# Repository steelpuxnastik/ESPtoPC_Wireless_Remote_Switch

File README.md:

# ESPtoPC Wireless Remote Switch

Remote power-on / reset / force-shutdown for a desktop PC over WiFi, using an ESP-12E board plugged into the motherboard's front-panel header, plus an OpenWrt app (LuCI page + CLI) to manage one or more of these boards. A variant of the board for the ESP-01 module is kept in the **esp-01-variant** branch of this repository.

Built for the case where a PC needs to be turned on remotely even after a power outage — before the OS is up, before Wake-on-LAN is usable — by literally pressing the physical power button in software.

## Repo layout

```
├── esptopc_poweron_remote_pcb/
│   ├── esptopc_poweron_remote_pcb.kicad_pro   KiCad project
│   ├── esptopc_poweron_remote_pcb.kicad_pcb   Board layout
│   ├── esptopc_poweron_remote_pcb.kicad_sch   Schematic
│   ├── esptopc_poweron_remote_pcb.kicad_prl   KiCad local project settings
│   ├── pinout_lib.kicad_sym                   Symbol library (front-panel connector J1)
│   └── pinout_lib.pretty/                     Footprint library (front-panel connector J1)
├── esptopc_poweron_remote/
│   └── esptopc_poweron_remote.ino             ESP8266 (ESP-12E) firmware
└── openwrt_program/
    └── deploy.sh                              One-shot installer for the OpenWrt side:
                                               LuCI app + CLI tool + handshake listener
```

## How it fits together

```
[ESP-12E board] --HTTP-->  [OpenWrt router]  <--LuCI/SSH--  [you]
   |    ^                     |
   |    |                     |-- LuCI page: device list, status, buttons
   |    `-- commands sent      -- CLI (`esptopcrsw`): menu + one-liners
   |        by OpenWrt         -- receives handshake/heartbeat from ESP
   `-- plugged into the PC's
       front-panel header,
       presses PWR_SW / RESET_SW
       and reads the power LED
```

- The ESP-12E runs its own tiny HTTP server (power on / force off / reset / status) and also announces itself to the router (MAC + a fixed identifying string) so it shows up in LuCI ready to be named and saved.
- The OpenWrt side is the "brain": it tracks device state, decides which buttons make sense to show (e.g. no point offering "Reset" on a PC that's already off), and is what you actually interact with — LuCI in a browser, or `esptopcrsw` over SSH.

## Hardware (KiCad project)

Open `esptopc_poweron_remote_pcb.kicad_pro` in KiCad. The board:

- Regulates the PC's 5V standby rail down to 3.3V (AMS1117-3.3) to power the ESP-12E;
- Uses two N-channel MOSFETs (Q1, Q2). When the ESP raises GPIO4 (Power) or GPIO5 (Reset) to HIGH, the transistor shorts the motherboard's **PWR_SW** or **RESET_SW** pin to ground, exactly like pressing the physical button. Pull-down resistors keep both transistors off while the ESP is starting;
- Reads the motherboard's power-LED line through an optocoupler (EL817) into GPIO13, to sense whether the PC is currently on (active-low: LOW = on). The optocoupler isolates the PC from the ESP: the PC can never hold a pin low during boot, so the board starts reliably after a reset, a brown-out or a power outage;
- Keeps the boot-mode pins at their standard levels with pull-up/pull-down resistors (GPIO0 and GPIO2 high, GPIO15 low). GPIO0 can be pulled to ground with jumper JP1 for flashing;
- Has a 4-pin header J2 (TX, RX, GND, 3.3V) for flashing and debugging.

### List of required components for board assembly

| Reference | Qty | Value | Footprint | Datasheet |
| :--- | :--- | :--- | :--- | :--- |
| **C1, C5** | 2 | 1uF | Capacitor_SMD:C_0805_2012Metric_Pad1.18x1.45mm_HandSolder | |
| **C2** | 1 | 22uF | Capacitor_Tantalum_SMD:CP_EIA-3528-21_Kemet-B_HandSolder | |
| **C3** | 1 | 150uF | Capacitor_Tantalum_SMD:CP_EIA-6032-28_Kemet-C_HandSolder | |
| **C4** | 1 | 100nF | Capacitor_SMD:C_1206_3216Metric_Pad1.33x1.80mm_HandSolder | |
| **H1, H2** | 2 | MountingHole M3 | MountingHole:MountingHole_3.2mm_M3 | |
| **J1** | 1 | 2x5 pin header (9 pins used) | pinout_lib:PinHeader_2x05_9pin_P2.54mm_Vertical | |
| **J2** | 1 | 1x4 pin header | Connector_PinHeader_2.54mm:PinHeader_1x04_P2.54mm_Vertical | |
| **JP1** | 1 | 1x2 pin header + jumper | Connector_PinHeader_2.54mm:PinHeader_1x02_P2.54mm_Vertical | |
| **Q1, Q2** | 2 | IRLML2502 | Package_TO_SOT_SMD:SOT-23_Handsoldering | |
| **R1, R2, R3, R4, R5, R6, R7** | 7 | 10k | Resistor_SMD:R_1206_3216Metric_Pad1.30x1.75mm_HandSolder | |
| **R8** | 1 | 330 | Resistor_SMD:R_0805_2012Metric_Pad1.20x1.40mm_HandSolder | |
| **R9** | 1 | 10k | Resistor_SMD:R_0805_2012Metric_Pad1.20x1.40mm_HandSolder | |
| **U1** | 1 | ESP-12E | RF_Module:ESP-12E | |
| **U2** | 1 | AMS1117-3.3 (fixed 3.3V version) | Package_TO_SOT_SMD:SOT-223-3_TabPin2 | [Datasheet](http://www.advanced-monolithic.com/pdf/ds1117.pdf) |
| **U3** | 1 | EL817 (optocoupler) | Package_DIP:DIP-4_W7.62mm | |

## Connection to PC

For through-connection of buttons to the motherboard, so that it would be possible not only to use the device to turn on the computer, but also, as before, to use the buttons, I recommend to use, for example, this type of DuPont splitter, you can find it on aliexpress or somewhere else.

You'll need, at least, 4 (four) of those cables for connection of all buttons and LED's for standard variant of connection. In computer cases where fewer buttons and LEDs are used, it is possible to use fewer of them so that you can connect only what you need.
As shown on picture, you need connect all wires exactly as it needs, even more, **you absolutely cannot make a mistake when connecting the button contacts PW+/- and RES+/- from the motherboard to the device, because the device is active component, and incorrect polarity will couse in a short circuit.** Same with LEDs. When connecting real buttons with pass-through connection, you don't have to observe polarity, as the buttons are passive components and have no polarity. But LEDs still needs to be properly connected. So I recommend double check all wires before turning on computer. If you have any doubts, I recommend that before connecting, you **apply the appropriate marks to all ends of the splitter**, similar to those present on the corresponding cables of the computer case (I made [special helper marking to print](print/connector_labels.pdf), so you can glue it to your connectors). Then you make sure that everything is applied correctly by checking everything with a multimeter or simply look at which wires go where and connect everything in accordance with your markings.

You can see on pictures, that variant of marking that used on female end of splitter is opposite (mirrored) polarity relative to the other ends. You can verify this with a multimeter, and you must verify this to ensure everything will be connected correctly. And you can use it as simple fast rule: 
1. decide what marking you need for female side with it's polarity;
2. use mirrored polarity marking for male ends of splitter;
3. verify with multimeter that polarity is right on ends and matches the markings you applied.

Also, as `J1` and `J2` I recommend not to search some special forms of sockets, but only to get this single row 1x40 of DuPont socket and just cut exactly count of pins you need from and and solder it. Yes, it will be a little scratched where it's cut, but it will work just fine. You can carefully file down the rough edges, but I wouldn't go to that much trouble for something as trivial as that.

In case of `J1` I recommend to cut 4pin-row, then 5pin-row, insert both of these rows simultaneously into the solder holes, align them (though they'll likely fit and align themselves without any problem, it's best to ensure there are no uneven areas or excess space), and only then solder them. As a result of all these not-so-tricky manipulations, we generally save significantly on the connections, which individually can cost significantly more than desired.

Connector `J1` (2x5, 9 pins used) repeats the pin order of the standard 9-pin front-panel header of a motherboard:

| J1 pin | Signal | Used for |
| :--- | :--- | :--- |
| 1 | HD+ | HDD LED plus: not used by the board, passed through to the case HDD LED |
| 2 | PLED+ | power-LED plus: read through the optocoupler |
| 3 | HD- | HDD LED minus: not used by the board, passed through to the case HDD LED |
| 4 | PLED- | power-LED minus: read through the optocoupler |
| 5 | RES- | ground of the RESET_SW header, also the ground of the whole board |
| 6 | PW+ | PWR_SW signal: closed to ground by Q1 |
| 7 | RES+ | RESET_SW signal: closed to ground by Q2 |
| 8 | PW- | ground of the PWR_SW header, also the ground of the whole board |
| 9 | +5Vsb | +5V standby, powers the board: must stay powered while the PC is off |

Front-panel header pinouts differ between motherboards, so check the manual of yours before connecting. Many motherboards have nothing on the header pin that corresponds to `+5Vsb`: in that case connect J1 pin 9 with a wire to a +5V standby source (for example the 5VSB line of the ATX power connector). The ground comes from `PW-`, the other pins need no extra connection.

Flashing connector `J2`: 

| J2 pin | Signal |
| :--- | :--- |
| 1 | TX (board output: connect to the RX of the USB-UART adapter) |
| 2 | RX (board input: connect to the TX of the USB-UART adapter) |
| 3 | GND |
| 4 | +3.3V |

Jumper `JP1` ("Prog") pulls GPIO0 to ground. Close it **before** power-up to start the ESP in flash mode, and remove it after flashing.

## Firmware (`esptopc_poweron_remote.ino`)

Flash with the Arduino IDE (ESP8266 core, board "Generic ESP8266 Module") via a 3.3V USB-serial adapter connected to `J2` (see **Connection to PC**). Close jumper `JP1` before powering the board, remove it after flashing. Power the board either from the PC (`J1` pin 9) or from the adapter's 3.3V pin, not from both at once.

Pins used by the firmware:

| GPIO | Role | Level |
| :--- | :--- | :--- |
| GPIO4 | Power button (Q1) | HIGH = pressed, LOW = released |
| GPIO5 | Reset button (Q2) | HIGH = pressed, LOW = released |
| GPIO13 | PC state (optocoupler) | LOW = PC on, HIGH = PC off |

Before flashing, edit near the top of the file:

- `WIFI_SSID` / `WIFI_PASS` — your network;
- `DEVICE_PASSWORD` — a shared password string. The board sends it to the router in the handshake (so the router knows it's one of yours), and it is also the seed of the per-device command key (see **Security** below). It must match `esptopcrsw.settings.password` on the router; the default `poweron-esp01` is already the same on both sides, so you don't have to change it;
- `POWER_SHORT_MS = 300` - A short press of the Power button. The configured press duration setting should work in most cases;
- `POWER_SOFTOFF_MS  = 4500` - Hold the Power button for the BIOS "soft-off delay" (e.g. Gigabyte: *Soft-Off by PWR-BTN = Delay 4 Sec*: a short press only suspends the PC, holding the button for 4+ seconds turns it off). It is only a fallback: the router normally sends its own time, see **Button press times** below;
- `POWER_FORCEOFF_MS = 5000` - Long-press the Power button to force the system unit to shut down. The required duration of the press can vary significantly between different computers; if it does not work, you will need to experiment to find the right timing;
- `RESET_SHORT_MS = 300` - A short press of the Reset button. The configured press duration setting should work in most cases;
- `WIFI_RETRY_MS = 30000` - While the board is not connected to WiFi (for example, the router is still booting after a power outage), it retries the connection every 30 seconds, forever;
- `HANDSHAKE_INTERVAL_MS = 10000` - Once the board is on WiFi, until the OpenWrt app acknowledges it, it announces itself every 10 seconds;
- `HEARTBEAT_INTERVAL_MS = 90000` - After the acknowledgment the board repeats the announcement every 90 seconds to show it is still alive.

How the heartbeat is used: the router stores the time of the last announcement in RAM, continuously, whether or not anyone has the LuCI page open. A device is shown as Offline if nothing was heard from it for 5 minutes. The PC's on/off state does not come from the heartbeat — it is read from the board only when you ask for it: when you open the LuCI page, press **Refresh status**, press any action button, or go through the CLI menus. Nothing is polled in the background. The only case with a wait is right after the router itself reboots: its RAM is empty, so a device shows as Offline until its next announcement (up to the heartbeat interval). A shorter `HEARTBEAT_INTERVAL_MS` shortens that wait.

The board finds the router automatically (`WiFi.gatewayIP()`, no IP to hardcode) and keeps retrying forever, so boot order after a power outage doesn't matter.

HTTP endpoints the board exposes (all require `?key=...`, see below):

| Endpoint         | Effect                        |
|-------------------|-------------------------------|
| `GET /power/on[?ms=N]`   | Short press of the power button (default `POWER_SHORT_MS`; limited to 100–2000) |
| `GET /power/hold[?ms=N]` | Hold the power button (default `POWER_SOFTOFF_MS`; limited to 500–10000) |
| `GET /power/off[?ms=N]`  | Long press, force shutdown (default `POWER_FORCEOFF_MS`; limited to 1000–15000) |
| `GET /reset[?ms=N]`      | Press of the reset button (default `RESET_SHORT_MS`; limited to 100–2000) |
| `GET /status`     | `{"pc_status":"on"\|"off"}`   |

All permission logic (e.g. "don't offer Reset while the PC is off") lives on the OpenWrt side, not in the firmware — the board just does what it's told and reports state.

## OpenWrt app (`deploy.sh`)

Self-contained installer — no package manager involved, just copies files to their real system paths and (re)starts the relevant services. Built against OpenWrt 25.x (APK-based, modern JSON-based LuCI menu/ACL — the classic Lua-controller style LuCI apps won't work the same way on this version).

### Install

On Windows, in CMD, I use this to copy `deploy.sh` to the router:
```CMD
scp X:\way\to\your\deploy.sh root@<router-ip>:/root/
```
After this, connect to the router over SSH and install the app:
```sh
ssh root@<router-ip>
sh deploy.sh
```

Re-running `deploy.sh` after an update is safe — it won't wipe devices you've already added (`/etc/config/esptopcrsw` is only created if missing).

What it sets up:
- LuCI page under **Services → ESPtoPC Wireless Remote Switch**: device table with status (On / Off / Offline) read on demand (when the page opens, on the **Refresh status** button and after each action; no background polling), buttons that adapt to state, a **Settings** button for per-device press times, add-device picker (from the router's DHCP client list or typed by hand), and a banner for boards that announced themselves but aren't saved yet (it has a Dismiss button; a dismissed board shows up again when it announces itself next time). **Initial setup and adding devices is carried out only in LuCI's ESPtoPC Wireless Remote Switch program page**;
- `esptopcrsw` CLI (see below; use it only after the setup in LuCI is done and checked);
- A second `uhttpd` instance on port 8090 that receives the handshake/heartbeat from ESP boards;
- `rpcd`/`ubus` backend (`/usr/libexec/rpcd/esptopcrsw`) that both the LuCI page and the CLI talk to.

### CLI

> **Important:**
> Use the CLI only after the program is set up in LuCI and you have checked that everything works as you expect: devices are added, the status is shown correctly, and the press times (the **Settings** button of each device) fit your PC. The CLI does not add devices or change settings, it only sends commands using what is configured in LuCI.

```sh
esptopcrsw                     # interactive menu, a convenient alternative to manual command entry
esptopcrsw list                # table of devices + status
esptopcrsw poweron <name>      # power on (or sleep, if already on)
esptopcrsw softoff <name>      # soft-off: hold Power for the BIOS delay (see below; `hold` is an alias)
esptopcrsw off <name>          # force power off (long hold)
esptopcrsw reset <name>
esptopcrsw check <name>        # check/restore connection
esptopcrsw help                # show help (list of commands and hints)
esptopcrsw lang [en|ru|uk]     # interface language (remembered)
```

Any of `poweron` / `softoff` / `off` / `reset` asks for a one-letter confirmation first (`y/N`) naming the device and the action, so a stray keypress can't send a command to the wrong PC. If a device looks offline when you run a command, the CLI tries to reconnect first and reports what happened, instead of failing silently.

### Button press times and Soft-Off

**Soft-Off is optional and aimed at Gigabyte boards.** Some Gigabyte BIOSes have *Soft-Off by PWR-BTN* (*Instant-Off* / *Delay 4 Sec*). With *Delay 4 Sec* a short press only suspends the PC, and a press held for 4 seconds shuts it down normally. If your board has no such option, you only need **Off / Sleep** and **Force Off**. The same action also covers any other case where the PC expects a Power press of a specific length: set that length as the hold time.

Power button actions, from shortest to longest: **Off / Sleep** (short press, what the PC does depends on its power settings), **Soft-Off (X s)** (hold for the BIOS soft-off delay), **Force Off** (long hold, `POWER_FORCEOFF_MS`), and **Reset**.

All press times are set per device in LuCI, in seconds, no reflashing needed: the **Settings** button in the device's *Manage* column (an empty field means the built-in value). The same options can be set with `uci` in the device section:

```sh
uci set esptopcrsw.@device[0].soft_off_ms='6000'    # the first device, ms
uci commit esptopcrsw
```

| Option | Action | Default | Allowed, ms |
|---|---|---|---|
| `power_short_ms` | Off / Sleep (short Power press) | 300 | 100–2000 |
| `soft_off_ms` | Soft-Off (Power hold for the BIOS delay) | 4500 | 500–10000 |
| `force_off_ms` | Force Off (long Power hold) | 5000 | 1000–15000 |
| `reset_ms` | Reset | 300 | 100–2000 |

The Soft-Off button label in LuCI and in the CLI shows the current value for that device. Unlike the short press, this button is not blocked in the first minute after power-on.

### Security

There's no login/password on the ESP's HTTP server itself — instead:

- **Handshake** (ESP → router): the board POSTs its MAC and `DEVICE_PASSWORD` to the router on boot/periodically, so the router knows it's genuinely this project's firmware announcing itself. It only filters out random devices, and it is sent in plain text.
- **Commands** (router → ESP): every `/power/on`, `/power/hold`, `/power/off`, `/reset`, `/status` call requires `?key=<12-hex-chars>`, computed as `md5(MAC:DEVICE_PASSWORD)` truncated to 12 characters — the same formula on both sides, so no separate secret needs to be distributed or synced per board. Each board gets a different key because its MAC is different. This stops a stray browser tab pointed at the board's IP from doing anything. It is **not** protection against someone who deliberately reads this repo (the formula and the default password are public), and it's **not encryption**: the key is part of the URL, so anyone sniffing the WiFi traffic can read it in plain text. Good enough for "don't let someone on the LAN poke it by accident", not meant to survive a hostile network. If you want more than the default, set your own string in `DEVICE_PASSWORD` in the firmware and in `uci set esptopcrsw.settings.password='...'` on the router.

## Known rough edges

- The rpcd/JS/LuCI layer was written against documented conventions for modern OpenWrt (menu.d/acl.d JSON, JS views over ubus) but hasn't been exhaustively tested beyond this one setup — if something in LuCI breaks after an OpenWrt upgrade, that's the first place to look.
- `busybox tr` on some builds doesn't support POSIX character classes (`[:lower:]`/`[:upper:]`) — the scripts here use explicit ranges (`a-z`/`A-Z`) everywhere for that reason; keep that in mind if you extend them.
- MAC addresses are stored/compared uppercase throughout, to avoid the same device getting registered twice under different casing.

## To-Do-List
- PCB variant based on ESP12E, that will be simpler in some areas in terms of harnessing components, plus it's protected by default from all the side effects that previously had to be addressed by monitoring the input from the PC's operating status pin. 
- Create a simplified default pass-through connection for all connectors, plus the ability to connect to the power supply with just one 5Vsb wire.

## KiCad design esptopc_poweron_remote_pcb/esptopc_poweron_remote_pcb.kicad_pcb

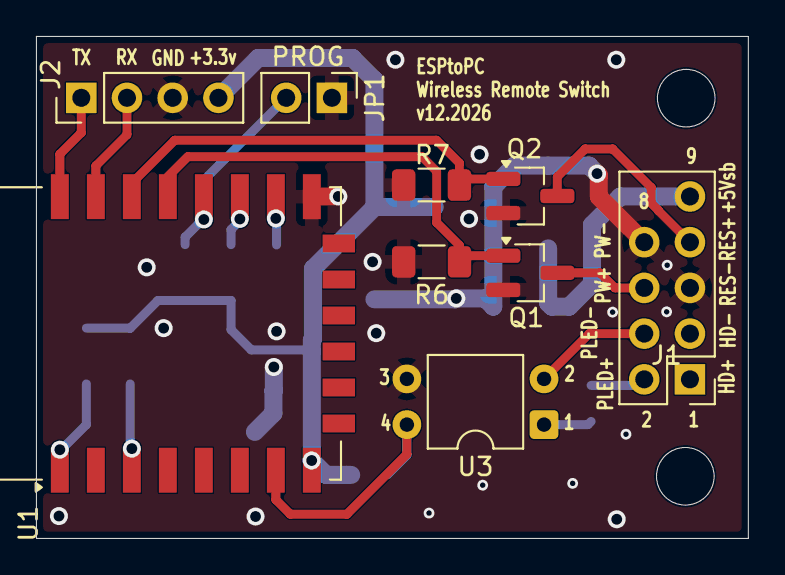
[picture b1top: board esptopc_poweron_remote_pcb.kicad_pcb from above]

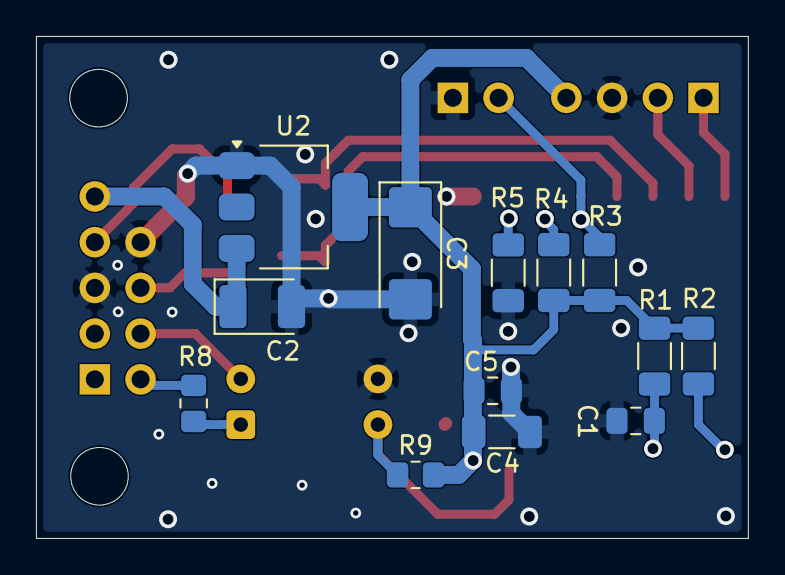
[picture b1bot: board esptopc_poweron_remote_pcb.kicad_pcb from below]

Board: 2 copper layers, 39.6 x 27.9 mm, 24 parts (13 on the bottom side), 18 nets.

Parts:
C1, C5: 1uf; C_0805_2012Metric_Pad1.18x1.45mm_HandSolder
C2: 22uF; CP_EIA-3528-21_Kemet-B_HandSolder
C3: 150uF; CP_EIA-6032-28_Kemet-C_HandSolder
C4: 100nf; C_1206_3216Metric_Pad1.33x1.80mm_HandSolder
H1, H2: MountingHole; MountingHole_3.2mm_M3
J1: Conn_02x05_9pin_motherboard_Odd_Even; PinHeader_2x05_9pin_P2.54mm_Vertical
J2: Conn_01x04; PinHeader_1x04_P2.54mm_Vertical
JP1: Prog; PinHeader_1x02_P2.54mm_Vertical
Q1, Q2: IRLML2502; SOT-23_Handsoldering
R1, R2, R3, R4, R5: 10k; R_1206_3216Metric_Pad1.30x1.75mm_HandSolder
R6, R7: 10K; R_1206_3216Metric_Pad1.30x1.75mm_HandSolder
R8: 330; R_0805_2012Metric_Pad1.20x1.40mm_HandSolder
R9: 10k; R_0805_2012Metric_Pad1.20x1.40mm_HandSolder
U1: ESP-12E
U2: AMS1117; SOT-223-3_TabPin2
U3: EL817; DIP-4_W7.62mm

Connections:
+3.3V: C3.1, C4.1, C5.1, J2.4, R1.1, R2.1, R3.2, R4.1, R9.2, U1.8 (VCC), U2.2 (VO)
+5Vsb_PC: C2.1, J1.9, U2.3 (VI)
ESP_MonitorPC: R9.1, U1.7 (GPIO13), U3.4
ESP_PowerPC: Q1.1 (G), R6.1, U1.19 (GPIO4)
ESP_ResetPC: Q2.1 (G), R7.1, U1.20 (GPIO5)
unnamed: R8.2, U3.1
unnamed: C1.1, R1.2, U1.3 (EN)
unnamed: JP1.2, R3.1, U1.18 (GPIO0)
unnamed: R4.2, U1.17 (GPIO2)
unnamed: R5.2, U1.16 (GPIO15)
unnamed: R2.2, U1.1 (~RST)
PLED+: J1.2, R8.1
PLED-: J1.4, U3.2
PW+: J1.6, Q1.3 (D)
PW-: C1.2, C2.2, C3.2, C4.2, C5.2, J1.5, J1.8, J2.3, JP1.1, Q1.2 (S), Q2.2 (S), R5.1, R6.2, R7.2, U1.15 (GND), U2.1 (ADJ), U3.3
RES+: J1.7, Q2.3 (D)
RX: J2.2, U1.21 (GPIO3/RXD)
TX: J2.1, U1.22 (GPIO1/TXD)

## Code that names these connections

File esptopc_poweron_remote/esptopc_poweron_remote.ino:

/*
 * ESP-12E: удалённое управление кнопками Power/Reset ПК через HTTP.
 * -----------------------------------------------------------------
 * GPIO4  -> затвор Q1 (Power button), N-канальный. HIGH = кнопка нажата, LOW = отпущена.
 * GPIO5  -> затвор Q2 (Reset button), N-канальный. HIGH = кнопка нажата, LOW = отпущена.
 * GPIO13 -> вход, статус ПК через оптрон U3 (EL817): LOW = ПК включен, HIGH = ПК выключен.
 *           Подтяжка к 3,3 В - R9 на плате.
 * GPIO0, GPIO2, GPIO15 - только режим загрузки (подтяжки R3, R4, R5), прошивкой не используются.
 *
 * TX/RX свободны (разъём J2 для прошивки и отладки), Serial при желании можно включать.
 *
 * HTTP-эндпоинты (без внутренних проверок — вся логика разрешений на OpenWrt):
 *   GET /power/on[?ms=N]  - короткое нажатие Power.
 *   GET /power/hold - удержание Power заданное время (BIOS «Soft-Off by PWR-BTN: Delay N Sec»).
 *                     Время: ?ms=N (роутер берёт из UCI soft_off_ms), без параметра - POWER_SOFTOFF_MS.
 *                     Нужно для плат Gigabyte с такой опцией и для любых ПК, которым нужно нажатие Power особой длины.
 *   GET /power/off[?ms=N] - длинное удержание Power (принудительное выключение).
 *   GET /reset[?ms=N]     - короткое нажатие Reset.
 *   GET /status     - {"pc_status":"on"|"off"}
 *
 * Плюс: ESP сама стучится на OpenWrt-программу (POST /announce на шлюз,
 * порт OPENWRT_PORT) - хендшейк раз в 10с до первого ack, потом
 * heartbeat раз в ~1.5 мин.
 */

#include <ESP8266WiFi.h>
#include <ESP8266WebServer.h>
#include <ESP8266HTTPClient.h>
#include <MD5Builder.h>

// ---- Настройки сети ----
const char* WIFI_SSID = "ВАШ_SSID";
const char* WIFI_PASS = "ВАШ_ПАРОЛЬ";

// ---- Пины ----
const uint8_t PIN_POWER     = 4;  // GPIO4  -> Q1 (Power), HIGH = нажато
const uint8_t PIN_RESET     = 5;  // GPIO5  -> Q2 (Reset), HIGH = нажато
const uint8_t PIN_PC_STATUS = 13; // GPIO13 <- оптрон U3 (LOW = ПК включён)


// ---- OpenWrt: хендшейк/heartbeat ----
const uint16_t OPENWRT_PORT = 8090;      // порт программы на роутере (сверим при написании OpenWrt-части)
const char* OPENWRT_PATH = "/cgi-bin/announce";  // единая точка приёма хендшейка/heartbeat
const char* DEVICE_PASSWORD = "poweron-esp01"; // общий пароль: метка в хендшейке + основа ключа команд md5(MAC:пароль); совпадает с uci get esptopcrsw.settings.password
const uint16_t HTTP_PORT = 80;           // наш собственный порт (для информации роутеру)

const uint32_t HANDSHAKE_INTERVAL_MS = 10000;  // пока не зарегистрированы - раз в 10с
const uint32_t HEARTBEAT_INTERVAL_MS = 90000;  // после регистрации - раз в 1.5 мин
const uint32_t WIFI_RETRY_MS = 30000;          // нет WiFi (роутер ещё не поднялся) - повторное подключение раз в 30с

bool registeredWithOpenWrt = false;
uint32_t lastAnnounceMs = 0;
uint32_t lastWifiRetryMs = 0;

// ---- Тайминги нажатий (мс) ----
// Это стартовые/безопасные значения (в т.ч. по ATX-спеке: >=4с на
// материнке гарантированно триггерит hard power-off).
// Для конкретной твоей мамки их стоит проверить и при необходимости
// подправить - вынесены отдельными константами специально для этого.
// Значения по умолчанию: используются, если роутер не передал ?ms=N
uint32_t POWER_SHORT_MS    = 300;   // короткое нажатие Power -> включение
uint32_t POWER_SOFTOFF_MS  = 4500;  // удержание Power для BIOS «Delay 4 Sec» (4 с + запас)
uint32_t POWER_FORCEOFF_MS = 5000;  // удержание Power -> принудительное выключение
uint32_t RESET_SHORT_MS    = 300;   // короткое нажатие Reset

// Допустимые границы ?ms= (те же, что на роутере)
const long POWER_SHORT_MIN_MS    = 100,  POWER_SHORT_MAX_MS    = 2000;
const long POWER_SOFTOFF_MIN_MS  = 500,  POWER_SOFTOFF_MAX_MS  = 10000;
const long POWER_FORCEOFF_MIN_MS = 1000, POWER_FORCEOFF_MAX_MS = 15000;
const long RESET_MIN_MS          = 100,  RESET_MAX_MS          = 2000;

ESP8266WebServer server(80);

bool pcIsOn() {
  return digitalRead(PIN_PC_STATUS) == LOW; // оптрон открыт, пока светодиод питания ПК горит
}

void pressButton(uint8_t pin, uint32_t durationMs) {
  digitalWrite(pin, HIGH); // MOSFET открыт - кнопка замкнута
  delay(durationMs);
  digitalWrite(pin, LOW);  // отпущена
 }

String commandKey() {
  MD5Builder md5;
  md5.begin();
  md5.add(WiFi.macAddress() + ":" + String(DEVICE_PASSWORD));
  md5.calculate();
  return md5.toString().substring(0, 12);
}

bool checkKey() {
  if (server.arg("key") != commandKey()) {
    server.send(403, "text/plain", "bad key");
    return false;
  }
  return true;
}

// Время нажатия: ?ms=N от роутера, ограниченное [minMs..maxMs]; без параметра - defMs
uint32_t requestMs(uint32_t defMs, long minMs, long maxMs) {
  long ms = server.hasArg("ms") ? server.arg("ms").toInt() : (long)defMs;
  if (ms < minMs) ms = minMs;
  if (ms > maxMs) ms = maxMs;
  return (uint32_t)ms;
}

void handlePowerOn() {
  if (!checkKey()) return;
  uint32_t ms = requestMs(POWER_SHORT_MS, POWER_SHORT_MIN_MS, POWER_SHORT_MAX_MS);
  pressButton(PIN_POWER, ms);
  server.send(200, "text/plain", String("Power short-press ") + String(ms) + " ms sent");
}

void handlePowerHold() {
  if (!checkKey()) return;
  uint32_t ms = requestMs(POWER_SOFTOFF_MS, POWER_SOFTOFF_MIN_MS, POWER_SOFTOFF_MAX_MS);
  pressButton(PIN_POWER, ms);
  server.send(200, "text/plain", String("Power soft-off hold ") + String(ms) + " ms sent");
}

void handlePowerOff() {
  if (!checkKey()) return;
  uint32_t ms = requestMs(POWER_FORCEOFF_MS, POWER_FORCEOFF_MIN_MS, POWER_FORCEOFF_MAX_MS);
  pressButton(PIN_POWER, ms);
  server.send(200, "text/plain", String("Power long-press (force off) ") + String(ms) + " ms sent");
}

void handleReset() {
  if (!checkKey()) return;
  uint32_t ms = requestMs(RESET_SHORT_MS, RESET_MIN_MS, RESET_MAX_MS);
  pressButton(PIN_RESET, ms);
  server.send(200, "text/plain", String("Reset press ") + String(ms) + " ms sent");
}

void handleStatus() {
  if (!checkKey()) return;
  server.send(200, "application/json",
    String("{\"pc_status\":\"") + (pcIsOn() ? "on" : "off") + "\"}");
}

void sendAnnounce() {
  WiFiClient client;
  HTTPClient http;
  String url = "http://" + WiFi.gatewayIP().toString() + ":" + String(OPENWRT_PORT) + OPENWRT_PATH;
  String payload = String("{\"mac\":\"") + WiFi.macAddress() +
                    "\",\"password\":\"" + DEVICE_PASSWORD +
                    "\",\"port\":" + String(HTTP_PORT) + "}";

  http.begin(client, url);
  http.addHeader("Content-Type", "application/json");
  int code = http.POST(payload);
  http.end();

  registeredWithOpenWrt = (code == 200);
  lastAnnounceMs = millis();
}

void setup() {
  // Кнопочные пины сразу в неактивное состояние (LOW), до WiFi.
  pinMode(PIN_POWER, OUTPUT);
  digitalWrite(PIN_POWER, LOW);
  pinMode(PIN_RESET, OUTPUT);
  digitalWrite(PIN_RESET, LOW);

  pinMode(PIN_PC_STATUS, INPUT); // внешний R9 уже подтягивает к 3,3 В, INPUT_PULLUP не нужен

  WiFi.mode(WIFI_STA);
  WiFi.begin(WIFI_SSID, WIFI_PASS);
  lastWifiRetryMs = millis();
  while (WiFi.status() != WL_CONNECTED) {
    delay(200); // без Serial - просто ждём, ретраи бесконечны
    if (millis() - lastWifiRetryMs >= WIFI_RETRY_MS) {
      lastWifiRetryMs = millis();
      WiFi.begin(WIFI_SSID, WIFI_PASS); // роутер ещё не поднялся - пробуем снова
    }
  }

  server.on("/power/on", HTTP_GET, handlePowerOn);
  server.on("/power/hold", HTTP_GET, handlePowerHold);
  server.on("/power/off", HTTP_GET, handlePowerOff);
  server.on("/reset", HTTP_GET, handleReset);
  server.on("/status", HTTP_GET, handleStatus);
  server.begin();
}

void loop() {
  server.handleClient();

  // Если WiFi отвалился - переподключаемся, не блокируя работу кнопок
  // дольше необходимого (begin() сам по себе не блокирующий).
  if (WiFi.status() != WL_CONNECTED) {
    registeredWithOpenWrt = false; // при обрыве WiFi - хендшейк заново
    if (millis() - lastWifiRetryMs >= WIFI_RETRY_MS) {
      lastWifiRetryMs = millis();
      WiFi.begin(WIFI_SSID, WIFI_PASS);
    }
    delay(100);
    return; // нет смысла стучаться в OpenWrt без WiFi
  }

  uint32_t now = millis();
  uint32_t interval = registeredWithOpenWrt ? HEARTBEAT_INTERVAL_MS : HANDSHAKE_INTERVAL_MS;
  if (now - lastAnnounceMs >= interval) {
    sendAnnounce();
  }
}
